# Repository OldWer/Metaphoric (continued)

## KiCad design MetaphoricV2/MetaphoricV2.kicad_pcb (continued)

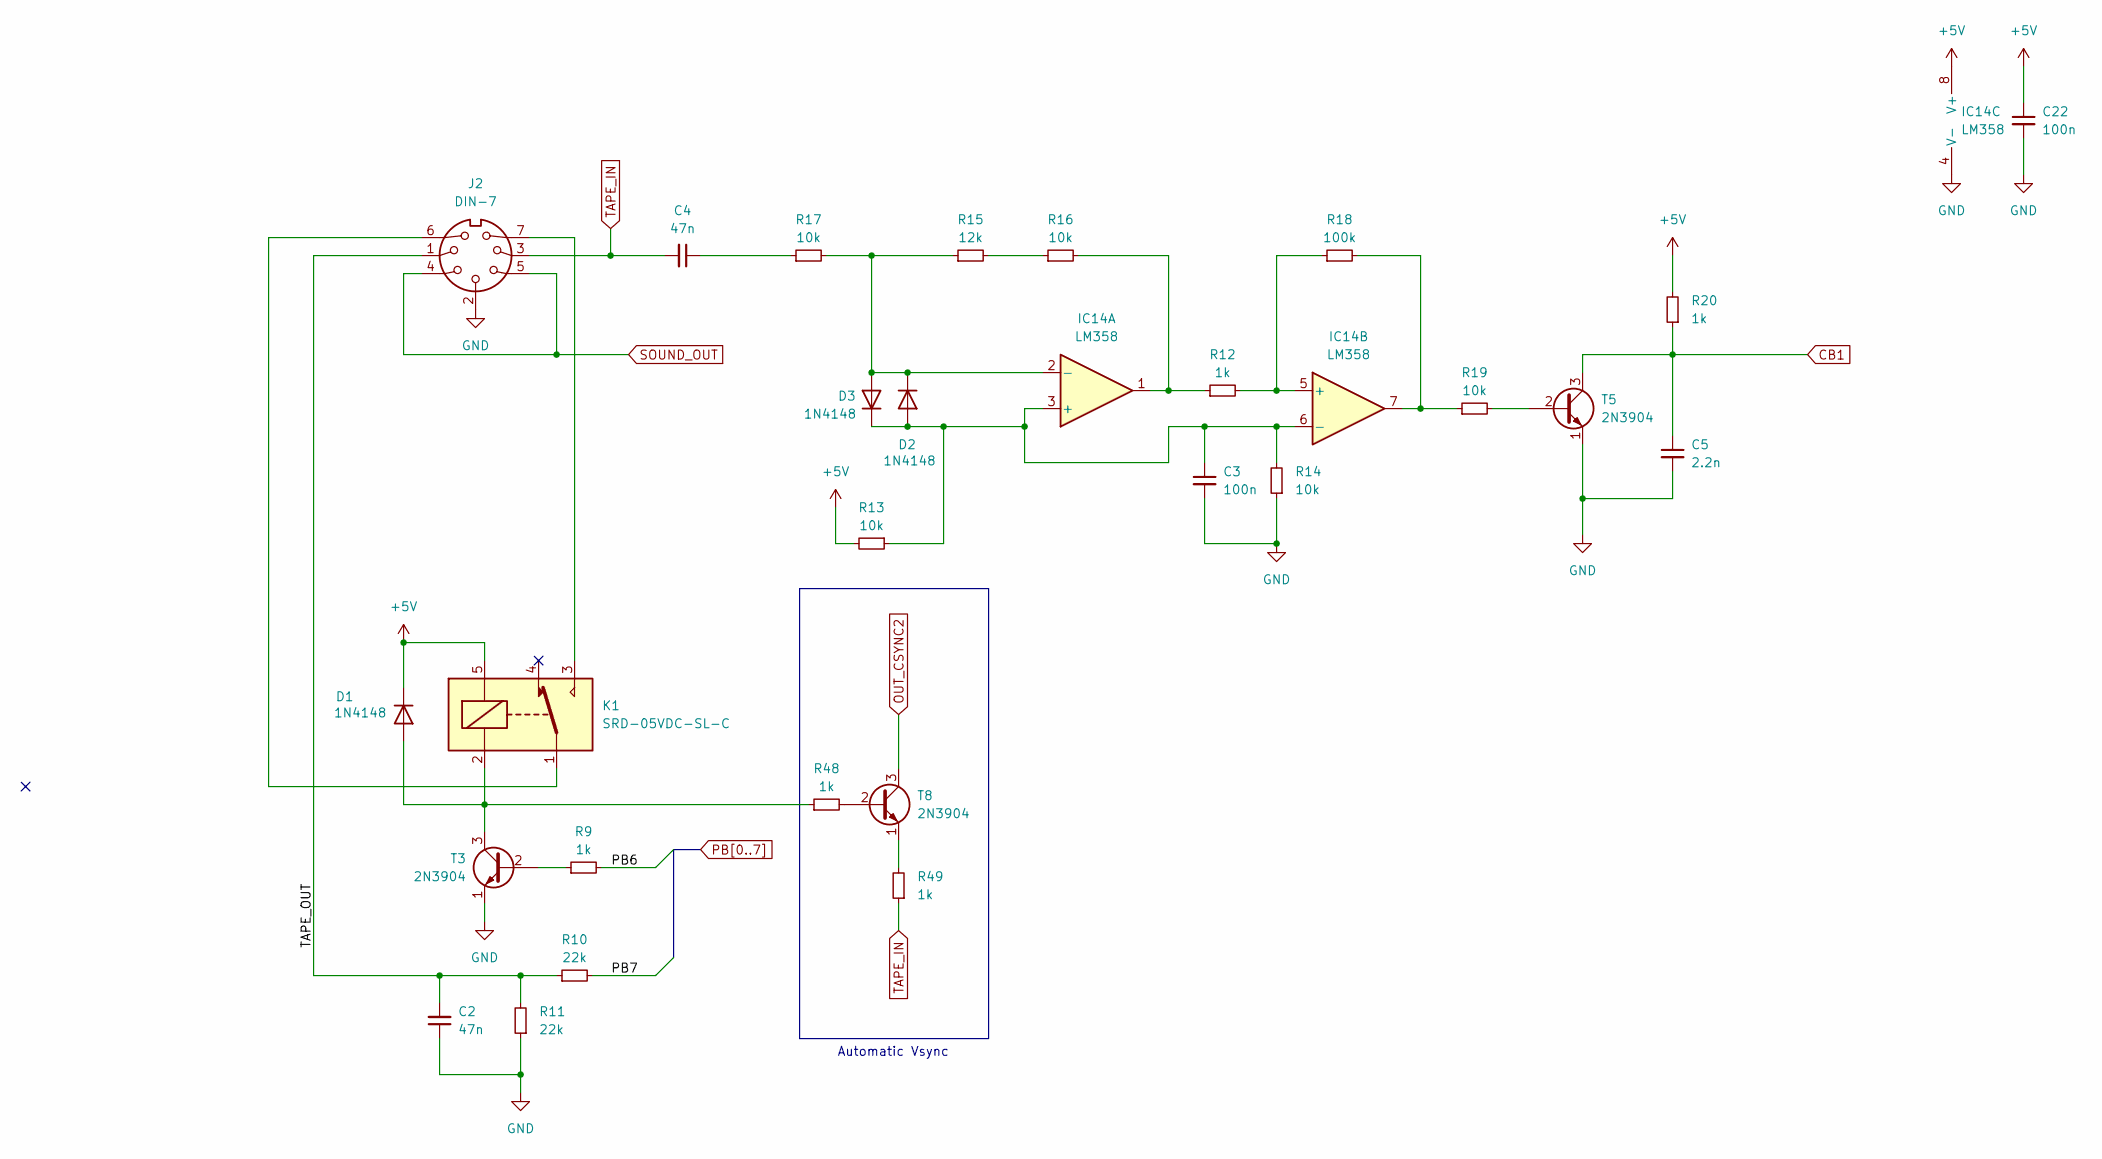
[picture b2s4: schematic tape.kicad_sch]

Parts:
C2, C4: 47n; C_Disc_D5.0mm_W2.5mm_P5.00mm
C3, C22: 100n; C_Disc_D5.0mm_W2.5mm_P5.00mm
C5: 2.2n; C_Disc_D5.0mm_W2.5mm_P5.00mm
D1, D2, D3: 1N4148; D_DO-35_SOD27_P7.62mm_Horizontal
IC14: LM358; DIP-8_W7.62mm_LongPads
J2: DIN-7; AV_CON_DIN7
K1: SRD-05VDC-SL-C; Relay_SPDT_SANYOU_SRD_Series_Form_C
R9, R12, R20, R48, R49: 1k; R_Axial_DIN0207_L6.3mm_D2.5mm_P7.62mm_Horizontal
R10, R11: 22k; R_Axial_DIN0207_L6.3mm_D2.5mm_P7.62mm_Horizontal
R13, R14, R16, R17, R19: 10k; R_Axial_DIN0207_L6.3mm_D2.5mm_P7.62mm_Horizontal
R15: 12k; R_Axial_DIN0207_L6.3mm_D2.5mm_P7.62mm_Horizontal
R18: 100k; R_Axial_DIN0207_L6.3mm_D2.5mm_P7.62mm_Horizontal
T3, T5, T8: 2N3904; TO-92_Inline

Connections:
+5V: C22.1, D1.1 (K), IC14.8 (V+), K1.5, R13.2, R20.2; also elsewhere on the board
/Tape/TAPE_OUT: C2.2, J2.1, R10.1, R11.2
CB1: C5.1, R20.1, T5.3 (C); also elsewhere on the board
GND: C2.1, C3.2, C5.2, C22.2, IC14.4 (V-), J2.2, R11.1, R14.1, T3.1 (E), T5.1 (E); also elsewhere on the board
unnamed: C4.1, R17.1
unnamed: D1.2 (A), K1.2, R48.1, T3.3 (C)
unnamed: C3.1, D2.2 (A), D3.1 (K), IC14.3 (+), IC14.6 (-), R13.1, R14.2
unnamed: D2.1 (K), D3.2 (A), IC14.2 (-), R15.1, R17.2
unnamed: IC14.1, R12.1, R16.2
unnamed: IC14.7, R18.2, R19.1
unnamed: IC14.5 (+), R12.2, R18.1
unnamed: J2.6, K1.1
unnamed: J2.7, K1.3
unnamed: R15.2, R16.1
unnamed: R9.1, T3.2 (B)
unnamed: R19.2, T5.2 (B)
unnamed: R48.2, T8.2 (B)
unnamed: R49.2, T8.1 (E)
OUT_CSYNC2: T8.3 (C); also elsewhere on the board
PB6: R9.2; also elsewhere on the board
PB7: R10.2; also elsewhere on the board
SOUND_OUT: J2.4, J2.5; also elsewhere on the board
TAPE_IN: C4.2, J2.3, R49.1

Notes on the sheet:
Automatic Vsync

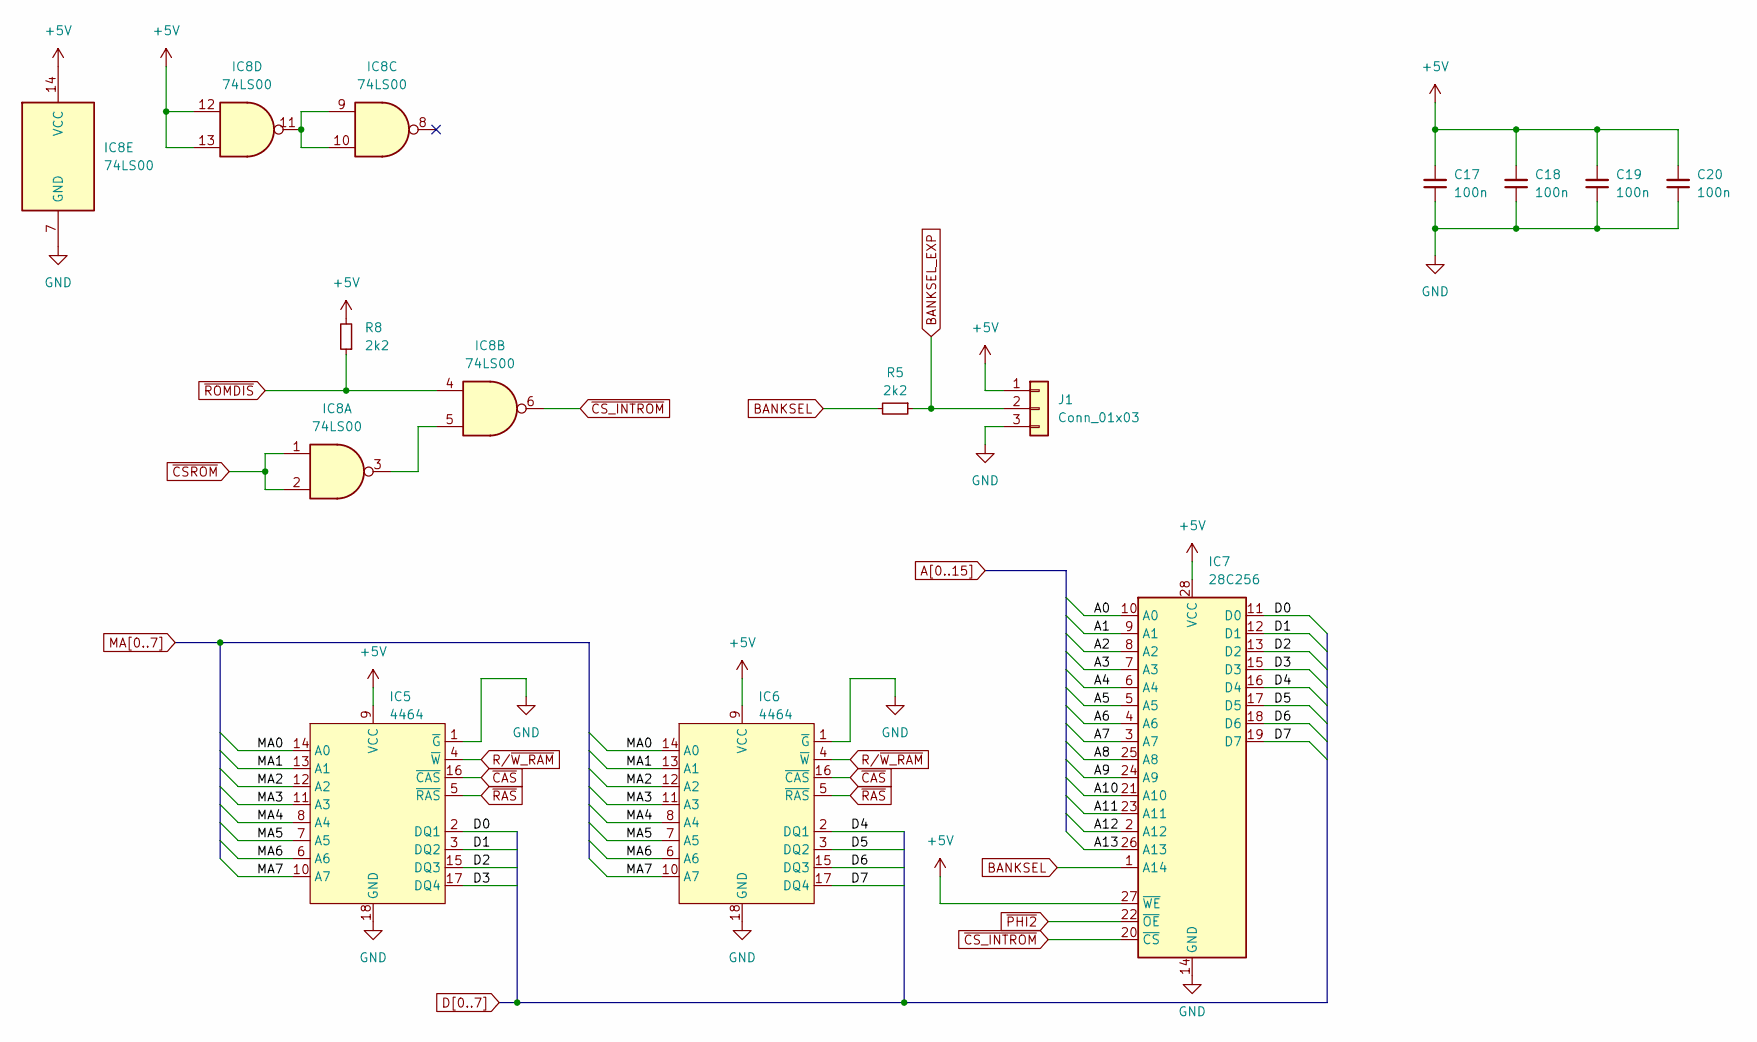
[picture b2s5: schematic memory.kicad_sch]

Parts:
C17, C18, C19, C20: 100n; C_Disc_D5.0mm_W2.5mm_P5.00mm
IC5, IC6: 4464; DIP-18_W7.62mm_LongPads
IC7: 28C256; DIP-28_W15.24mm_LongPads
IC8: 74LS00; DIP-14_W7.62mm_LongPads
J1: Conn_01x03; PinHeader_1x03_P2.54mm_Vertical
R5, R8: 2k2; R_Axial_DIN0207_L6.3mm_D2.5mm_P7.62mm_Horizontal

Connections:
+5V: C17.2, C18.2, C19.2, C20.2, IC5.9 (VCC), IC6.9 (VCC), IC7.27 (~WE), IC7.28 (VCC), IC8.12, IC8.13, IC8.14 (VCC), J1.1, R8.2; also elsewhere on the board
A0: IC7.10 (A0); also elsewhere on the board
A1: IC7.9 (A1); also elsewhere on the board
A2: IC7.8 (A2); also elsewhere on the board
A3: IC7.7 (A3); also elsewhere on the board
A4: IC7.6 (A4); also elsewhere on the board
A5: IC7.5 (A5); also elsewhere on the board
A6: IC7.4 (A6); also elsewhere on the board
A7: IC7.3 (A7); also elsewhere on the board
A8: IC7.25 (A8); also elsewhere on the board
A9: IC7.24 (A9); also elsewhere on the board
A10: IC7.21 (A10); also elsewhere on the board
A11: IC7.23 (A11); also elsewhere on the board
A12: IC7.2 (A12); also elsewhere on the board
A13: IC7.26 (A13); also elsewhere on the board
BANKSEL: IC7.1 (A14), R5.2
BANKSEL_EXP: J1.2, R5.1; also elsewhere on the board
D0: IC5.2 (DQ1), IC7.11 (D0); also elsewhere on the board
D1: IC5.3 (DQ2), IC7.12 (D1); also elsewhere on the board
D2: IC5.15 (DQ3), IC7.13 (D2); also elsewhere on the board
D3: IC5.17 (DQ4), IC7.15 (D3); also elsewhere on the board
D4: IC6.2 (DQ1), IC7.16 (D4); also elsewhere on the board
D5: IC6.3 (DQ2), IC7.17 (D5); also elsewhere on the board
D6: IC6.15 (DQ3), IC7.18 (D6); also elsewhere on the board
D7: IC6.17 (DQ4), IC7.19 (D7); also elsewhere on the board
GND: C17.1, C18.1, C19.1, C20.1, IC5.1 (~G), IC5.18 (GND), IC6.1 (~G), IC6.18 (GND), IC7.14 (GND), IC8.7 (GND), J1.3; also elsewhere on the board
MA0: IC5.14 (A0), IC6.14 (A0); also elsewhere on the board
MA1: IC5.13 (A1), IC6.13 (A1); also elsewhere on the board
MA2: IC5.12 (A2), IC6.12 (A2); also elsewhere on the board
MA3: IC5.11 (A3), IC6.11 (A3); also elsewhere on the board
MA4: IC5.8 (A4), IC6.8 (A4); also elsewhere on the board
MA5: IC5.7 (A5), IC6.7 (A5); also elsewhere on the board
MA6: IC5.6 (A6), IC6.6 (A6); also elsewhere on the board
MA7: IC5.10 (A7), IC6.10 (A7); also elsewhere on the board
unnamed: IC8.3, IC8.5
unnamed: IC8.9, IC8.10, IC8.11
R/~W_RAM: IC5.4 (~W), IC6.4 (~W); also elsewhere on the board
~CAS: IC5.16 (~CAS), IC6.16 (~CAS); also elsewhere on the board
~CSROM: IC8.1, IC8.2; also elsewhere on the board
~CS_INTROM: IC7.20 (~CS), IC8.6
~PHI2: IC7.22 (~OE); also elsewhere on the board
~RAS: IC5.5 (~RAS), IC6.5 (~RAS); also elsewhere on the board
~ROMDIS: IC8.4, R8.1; also elsewhere on the board

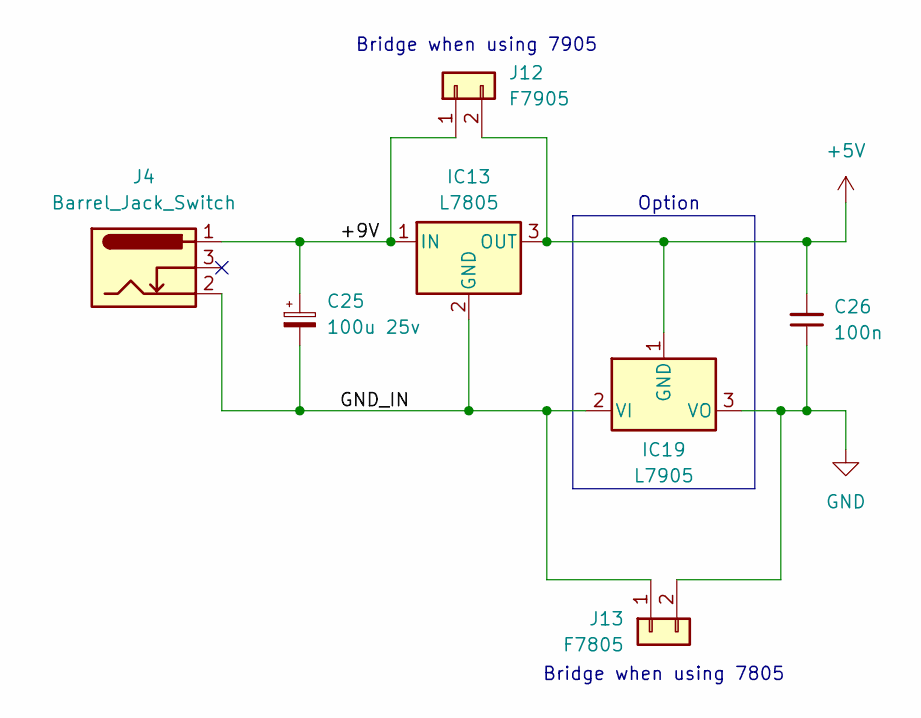
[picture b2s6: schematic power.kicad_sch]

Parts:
C25: 100u 25v; CP_Radial_D8.0mm_P3.50mm
C26: 100n; C_Disc_D5.0mm_W2.5mm_P5.00mm
IC13: L7805; TO-220-3_Vertical
IC19: L7905; TO-220-3_Vertical
J4: Barrel_Jack_Switch; BarrelJack_Horizontal
J12: F7905; PinHeader_1x02_P2.54mm_Vertical
J13: F7805; PinHeader_1x02_P2.54mm_Vertical

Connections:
+5V: C26.2, IC13.3 (OUT), IC19.1 (GND), J12.2; also elsewhere on the board
/Power/+9V: C25.1, IC13.1 (IN), J4.1, J12.1
/Power/GND_IN: C25.2, IC13.2 (GND), IC19.2 (VI), J4.2, J13.1
GND: C26.1, IC19.3 (VO), J13.2; also elsewhere on the board

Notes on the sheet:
Bridge when using 7805
Option
Bridge when using 7905

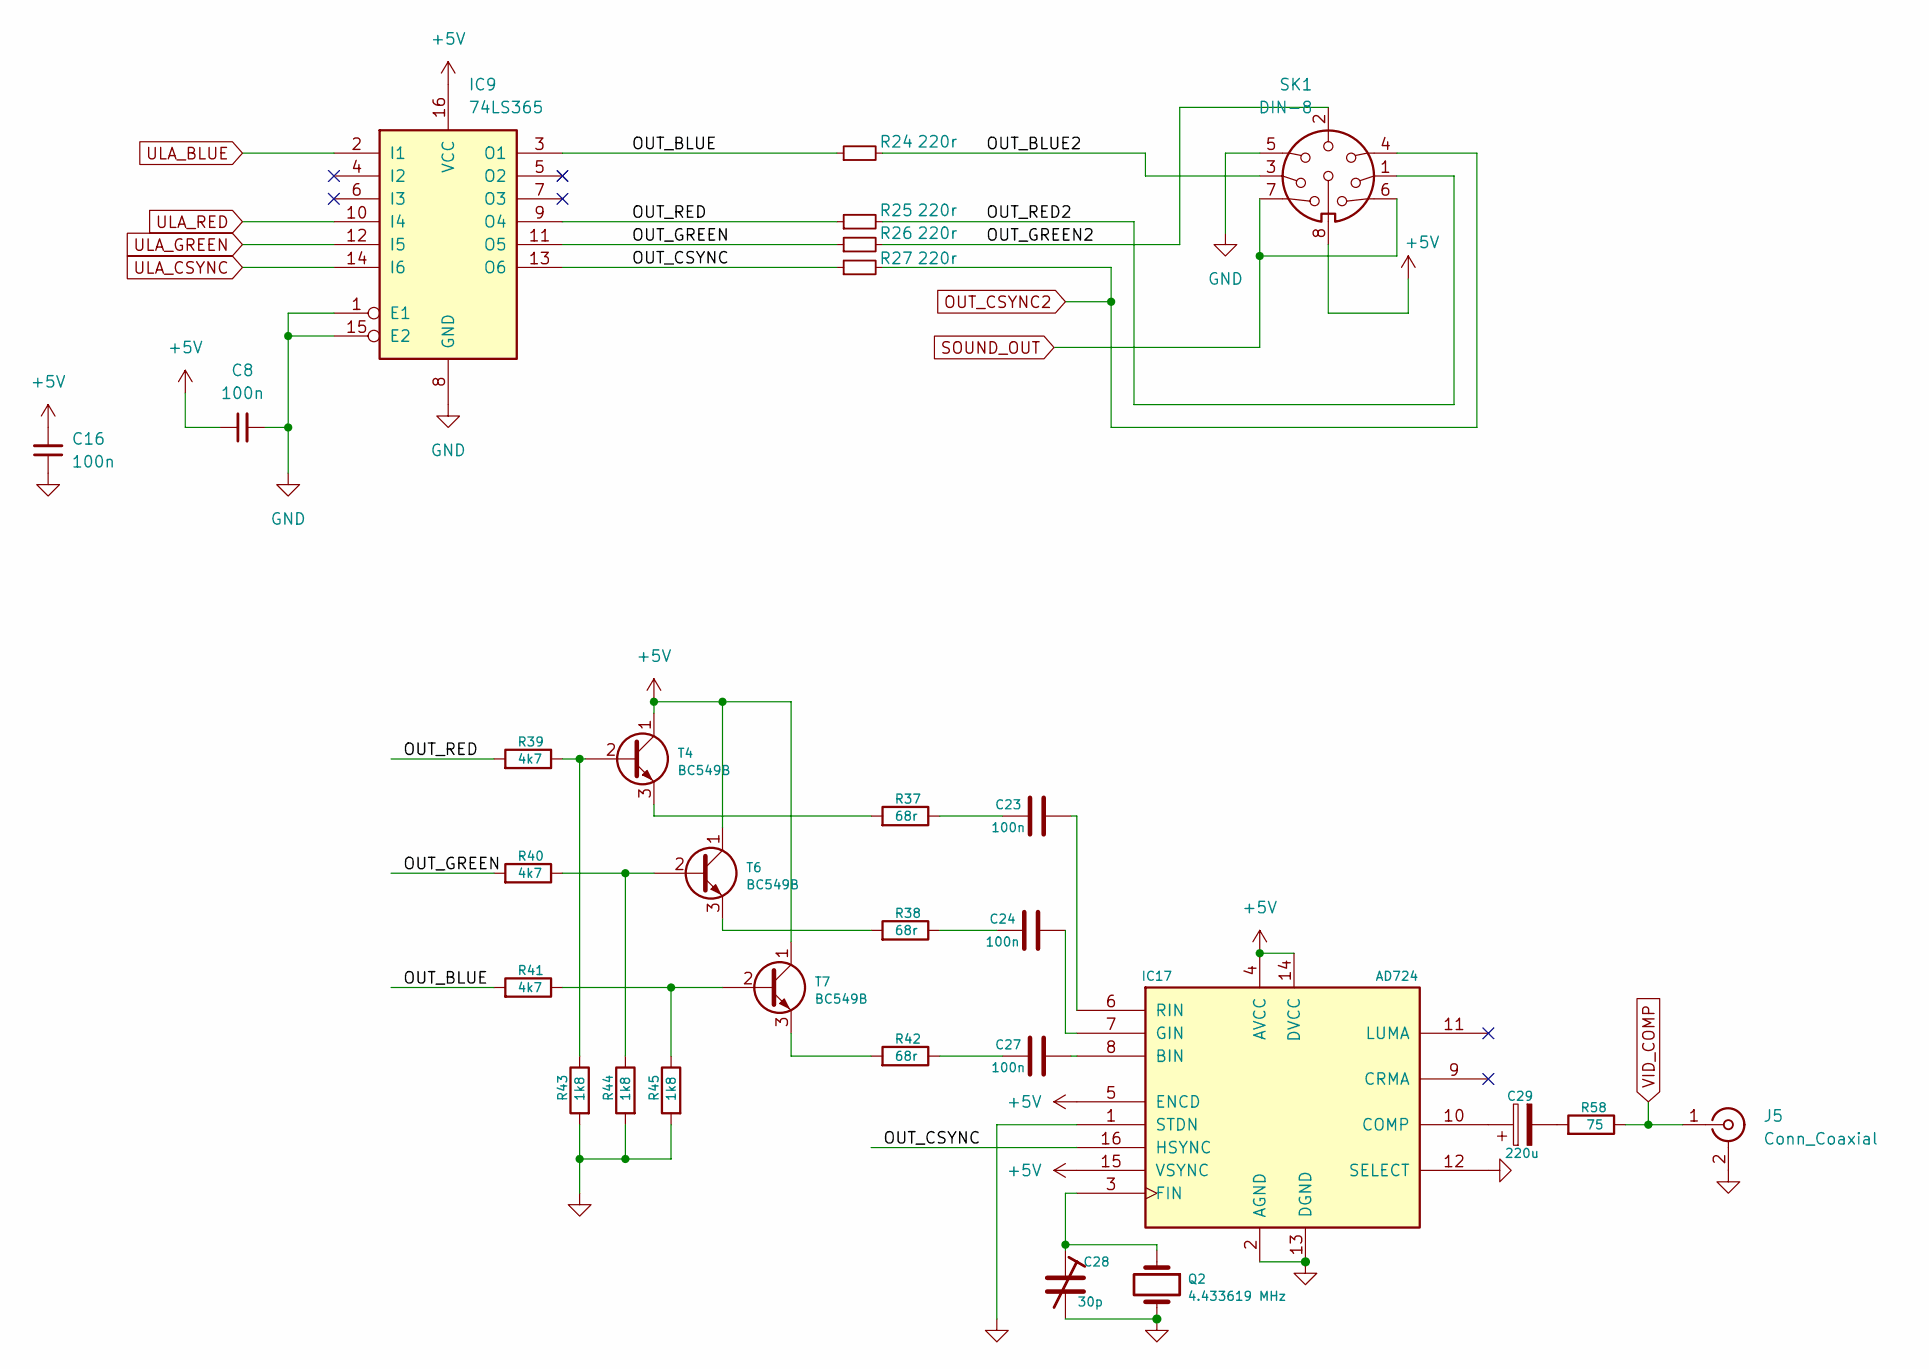
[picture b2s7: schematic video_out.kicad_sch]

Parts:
C8, C16, C23, C24, C27: 100n; C_Disc_D5.0mm_W2.5mm_P5.00mm
C28: 30p; C_Trim_D6.3mm_P5.50mm
C29: 220u; CP_Radial_D5.0mm_P2.50mm
IC9: 74LS365; DIP-16_W7.62mm_LongPads
IC17: AD724; SOIC-16W_7.5x10.3mm_P1.27mm
J5: Conn_Coaxial; Composite_RCA
Q2: 4.433619 MHz; Crystal_HC49-U_Vertical
R24, R25, R26, R27: 220r; R_Axial_DIN0207_L6.3mm_D2.5mm_P7.62mm_Horizontal
R37, R38, R42: 68r; R_Axial_DIN0207_L6.3mm_D2.5mm_P7.62mm_Horizontal
R39, R40, R41: 4k7; R_Axial_DIN0207_L6.3mm_D2.5mm_P7.62mm_Horizontal
R43, R44, R45: 1k8; R_Axial_DIN0207_L6.3mm_D2.5mm_P7.62mm_Horizontal
R58: 75; R_Axial_DIN0207_L6.3mm_D2.5mm_P7.62mm_Horizontal
SK1: DIN-8; AV_CON_DIN8
T4, T6, T7: BC549B; TO-92

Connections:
+5V: C8.1, C16.2, IC9.16 (VCC), IC17.4 (AVCC), IC17.5 (ENCD), IC17.14 (DVCC), IC17.15 (VSYNC), SK1.8, T4.1 (C), T6.1 (C), T7.1 (C); also elsewhere on the board
/Video Out/OUT_BLUE: IC9.3 (O1), R24.1, R41.2
/Video Out/OUT_BLUE2: R24.2, SK1.3
/Video Out/OUT_CSYNC: IC9.13 (O6), IC17.16 (HSYNC), R27.1
/Video Out/OUT_GREEN: IC9.11 (O5), R26.1, R40.2
/Video Out/OUT_GREEN2: R26.2, SK1.2
/Video Out/OUT_RED: IC9.9 (O4), R25.1, R39.2
/Video Out/OUT_RED2: R25.2, SK1.1
GND: C8.2, C16.1, C28.2, IC9.1 (E1), IC9.8 (GND), IC9.15 (E2), IC17.1 (STDN), IC17.2 (AGND), IC17.12 (SELECT), IC17.13 (DGND), J5.2 (Ext), Q2.2, R43.2, R44.2, R45.2, SK1.5; also elsewhere on the board
unnamed: C23.1, R37.1
unnamed: C24.1, R38.1
unnamed: C27.1, R42.1
unnamed: C29.2, R58.2
unnamed: C27.2, IC17.8 (BIN)
unnamed: C29.1, IC17.10 (COMP)
unnamed: C28.1, IC17.3 (FIN), Q2.1
unnamed: C24.2, IC17.7 (GIN)
unnamed: C23.2, IC17.6 (RIN)
unnamed: R39.1, R43.1, T4.2 (B)
unnamed: R37.2, T4.3 (E)
unnamed: R40.1, R44.1, T6.2 (B)
unnamed: R38.2, T6.3 (E)
unnamed: R41.1, R45.1, T7.2 (B)
unnamed: R42.2, T7.3 (E)
OUT_CSYNC2: R27.2, SK1.4; also elsewhere on the board
SOUND_OUT: SK1.6, SK1.7; also elsewhere on the board
ULA_BLUE: IC9.2 (I1); also elsewhere on the board
ULA_CSYNC: IC9.14 (I6); also elsewhere on the board
ULA_GREEN: IC9.12 (I5); also elsewhere on the board
ULA_RED: IC9.10 (I4); also elsewhere on the board
VID_COMP: J5.1 (In), R58.1; also elsewhere on the board

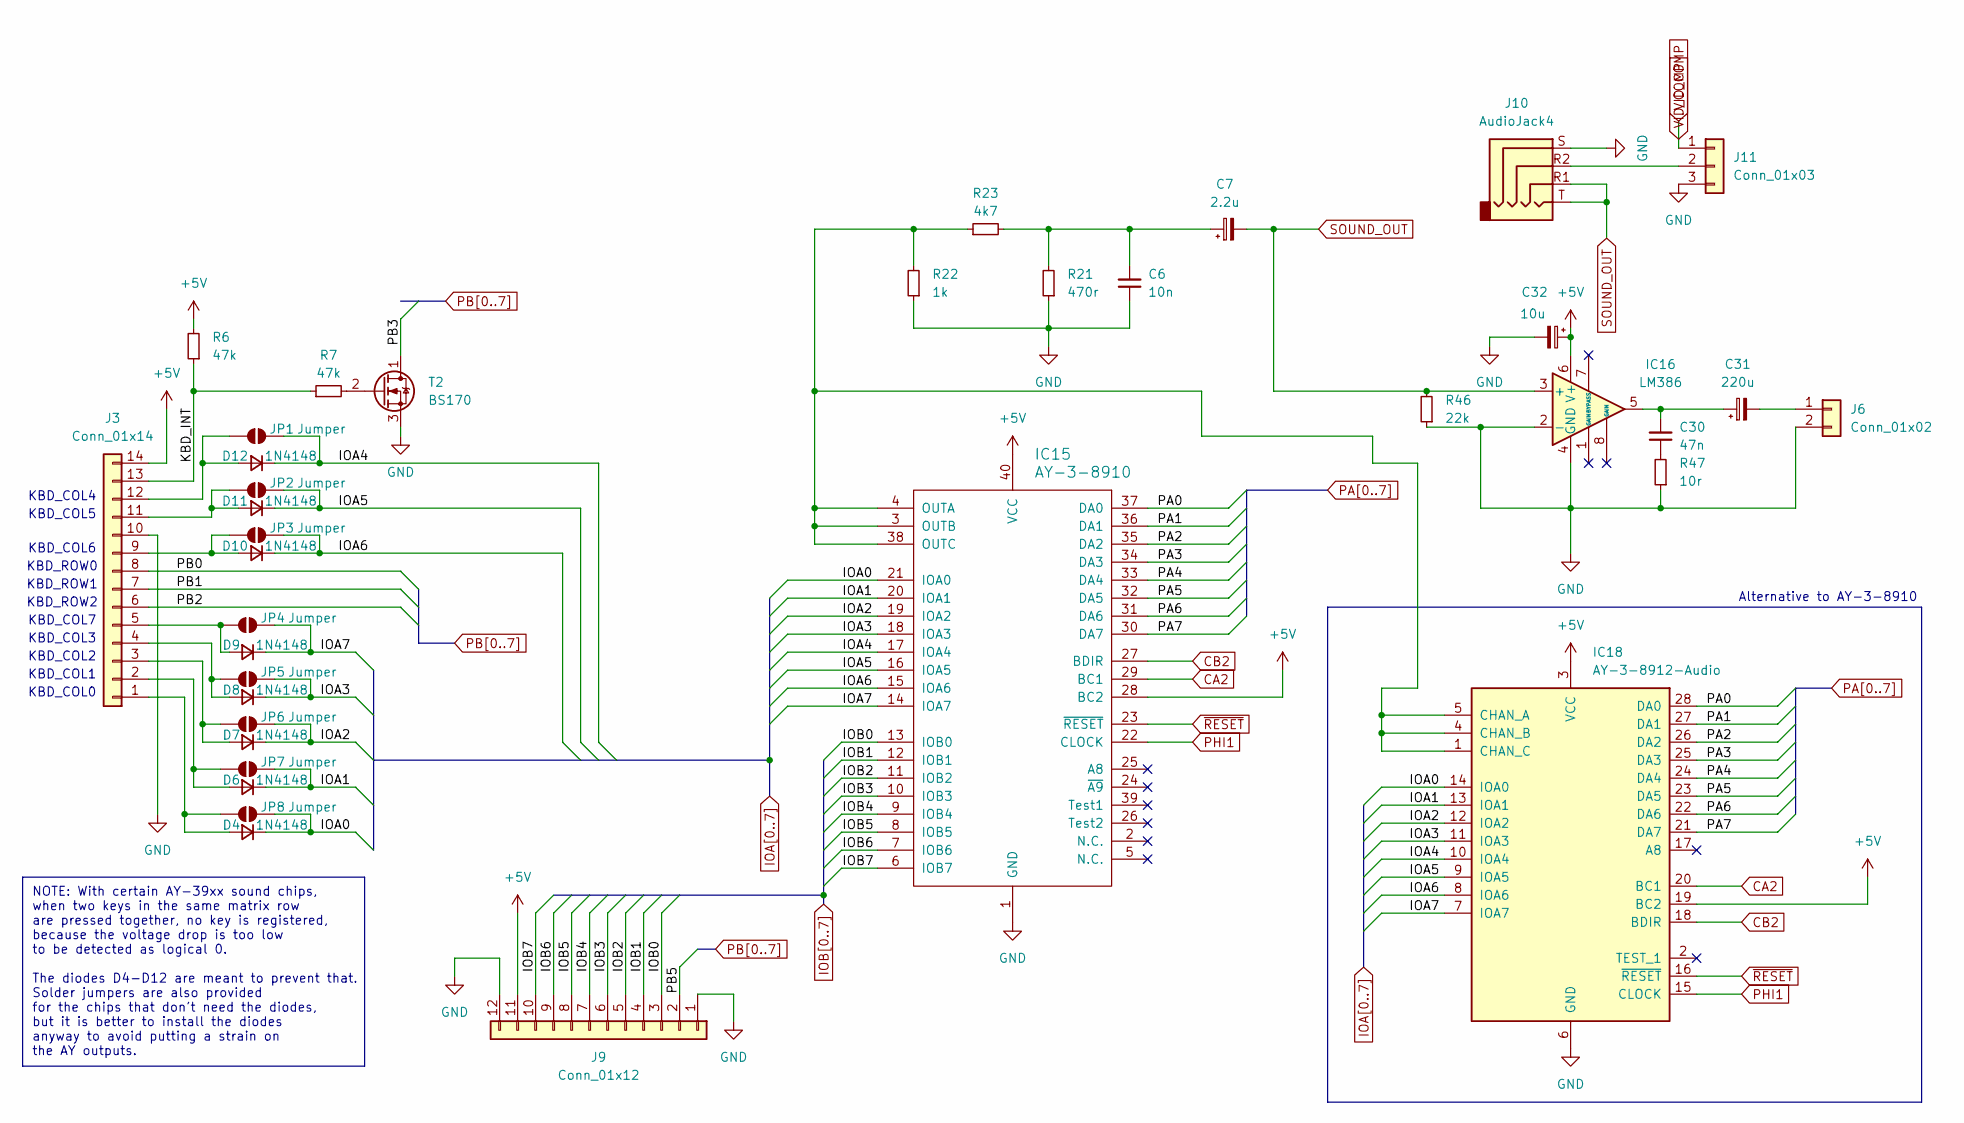
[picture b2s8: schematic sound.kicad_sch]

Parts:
C6: 10n; C_Disc_D5.0mm_W2.5mm_P5.00mm
C7: 2.2u; CP_Radial_D5.0mm_P2.50mm
C30: 47n; C_Disc_D5.0mm_W2.5mm_P5.00mm
C31: 220u; CP_Radial_D5.0mm_P2.50mm
C32: 10u; CP_Radial_D5.0mm_P2.50mm
D4, D6, D7, D8, D9, D10, D11, D12: 1N4148; D_DO-35_SOD27_P7.62mm_Horizontal
IC15: AY-3-8910; DIP-40_W15.24mm_LongPads
IC16: LM386; DIP-8_W7.62mm
IC18: AY-3-8912-Audio; DIP-28_W15.24mm_LongPads
J3: Conn_01x14; PinHeader_1x14_P2.54mm_Vertical
J6: Conn_01x02; PinHeader_1x02_P2.54mm_Vertical
J9: Conn_01x12; PinHeader_1x12_P2.54mm_Vertical
J10: AudioJack4; PJ-322
J11: Conn_01x03; PinHeader_1x03_P2.54mm_Vertical
JP1, JP2, JP3, JP4, JP5, JP6, JP7, JP8: Jumper; SolderJumper-2_P1.3mm_Open_RoundedPad1.0x1.5mm
R6, R7: 47k; R_Axial_DIN0207_L6.3mm_D2.5mm_P7.62mm_Horizontal
R21: 470r; R_Axial_DIN0207_L6.3mm_D2.5mm_P7.62mm_Horizontal
R22: 1k; R_Axial_DIN0207_L6.3mm_D2.5mm_P7.62mm_Horizontal
R23: 4k7; R_Axial_DIN0207_L6.3mm_D2.5mm_P7.62mm_Horizontal
R46: 22k; R_Axial_DIN0207_L6.3mm_D2.5mm_P7.62mm_Horizontal
R47: 10r; R_Axial_DIN0207_L6.3mm_D2.5mm_P7.62mm_Horizontal
T2: BS170; TO-92_Inline

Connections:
+5V: C32.1, IC15.28 (BC2), IC15.40 (VCC), IC16.6 (V+), IC18.3 (VCC), IC18.19 (BC2), J3.14, J9.11, R6.2; also elsewhere on the board
/Sound/KBD_INT: J3.13, R6.1, R7.1
CA2: IC15.29 (BC1), IC18.20 (BC1); also elsewhere on the board
CB2: IC15.27 (BDIR), IC18.18 (BDIR); also elsewhere on the board
GND: C6.1, C32.2, IC15.1 (GND), IC16.2 (-), IC16.4 (GND), IC18.6 (GND), J3.10, J6.2, J9.1, J9.12, J10.S, J11.3, R21.1, R22.1, R46.1, R47.1, T2.3 (S); also elsewhere on the board
IOA0: D4.1 (K), IC15.21 (IOA0), IC18.14 (IOA0), JP8.2 (B)
IOA1: D6.1 (K), IC15.20 (IOA1), IC18.13 (IOA1), JP7.2 (B)
IOA2: D7.1 (K), IC15.19 (IOA2), IC18.12 (IOA2), JP6.2 (B)
IOA3: D8.1 (K), IC15.18 (IOA3), IC18.11 (IOA3), JP5.2 (B)
IOA4: D12.1 (K), IC15.17 (IOA4), IC18.10 (IOA4), JP1.2 (B)
IOA5: D11.1 (K), IC15.16 (IOA5), IC18.9 (IOA5), JP2.2 (B)
IOA6: D10.1 (K), IC15.15 (IOA6), IC18.8 (IOA6), JP3.2 (B)
IOA7: D9.1 (K), IC15.14 (IOA7), IC18.7 (IOA7), JP4.2 (B)
IOB0: IC15.13 (IOB0), J9.3
IOB1: IC15.12 (IOB1), J9.4
IOB2: IC15.11 (IOB2), J9.5
IOB3: IC15.10 (IOB3), J9.6
IOB4: IC15.9 (IOB4), J9.7
IOB5: IC15.8 (IOB5), J9.8
IOB6: IC15.7 (IOB6), J9.9
IOB7: IC15.6 (IOB7), J9.10
unnamed: C6.2, C7.1, R21.2, R23.2
unnamed: C30.1, R47.2
unnamed: C30.2, C31.1, IC16.5
unnamed: D4.2 (A), J3.1, JP8.1 (A)
unnamed: D6.2 (A), J3.2, JP7.1 (A)
unnamed: D7.2 (A), J3.3, JP6.1 (A)
unnamed: D8.2 (A), J3.4, JP5.1 (A)
unnamed: D9.2 (A), J3.5, JP4.1 (A)
unnamed: D10.2 (A), J3.9, JP3.1 (A)
unnamed: D11.2 (A), J3.11, JP2.1 (A)
unnamed: D12.2 (A), J3.12, JP1.1 (A)
unnamed: IC15.3 (OUTB), IC15.4 (OUTA), IC15.38 (OUTC), IC18.1 (CHAN_C), IC18.4 (CHAN_B), IC18.5 (CHAN_A), R22.2, R23.1
unnamed: C31.2, J6.1
unnamed: J10.R2, J11.2
unnamed: R7.2, T2.2 (G)
PA0: IC15.37 (DA0), IC18.28 (DA0); also elsewhere on the board
PA1: IC15.36 (DA1), IC18.27 (DA1); also elsewhere on the board
PA2: IC15.35 (DA2), IC18.26 (DA2); also elsewhere on the board
PA3: IC15.34 (DA3), IC18.25 (DA3); also elsewhere on the board
PA4: IC15.33 (DA4), IC18.24 (DA4); also elsewhere on the board
PA5: IC15.32 (DA5), IC18.23 (DA5); also elsewhere on the board
PA6: IC15.31 (DA6), IC18.22 (DA6); also elsewhere on the board
PA7: IC15.30 (DA7), IC18.21 (DA7); also elsewhere on the board
PB0: J3.8; also elsewhere on the board
PB1: J3.7; also elsewhere on the board
PB2: J3.6; also elsewhere on the board
PB3: T2.1 (D); also elsewhere on the board
PB5: J9.2; also elsewhere on the board
PHI1: IC15.22 (CLOCK), IC18.15 (CLOCK); also elsewhere on the board
SOUND_OUT: C7.2, IC16.3 (+), J10.R1, J10.T, R46.2; also elsewhere on the board
VID_COMP: J11.1; also elsewhere on the board
~RESET: IC15.23 (~RESET), IC18.16 (~RESET); also elsewhere on the board

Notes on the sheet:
NOTE: With certain AY-39xx sound chips, when two keys in the same matrix row are pressed together, no key is registered, because the voltage drop is too low to be detected as logical 0. The diodes D4-D12 are meant to prevent that. Solder jumpers are also provided for the chips that don't need the d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
KBD_COL6
KBD_COL4
KBD_ROW0
KBD_ROW2
KBD_COL0
Alternative to AY-3-8910
KBD_COL3
KBD_ROW1
KBD_COL7
KBD_COL1
KBD_COL5
KBD_COL2

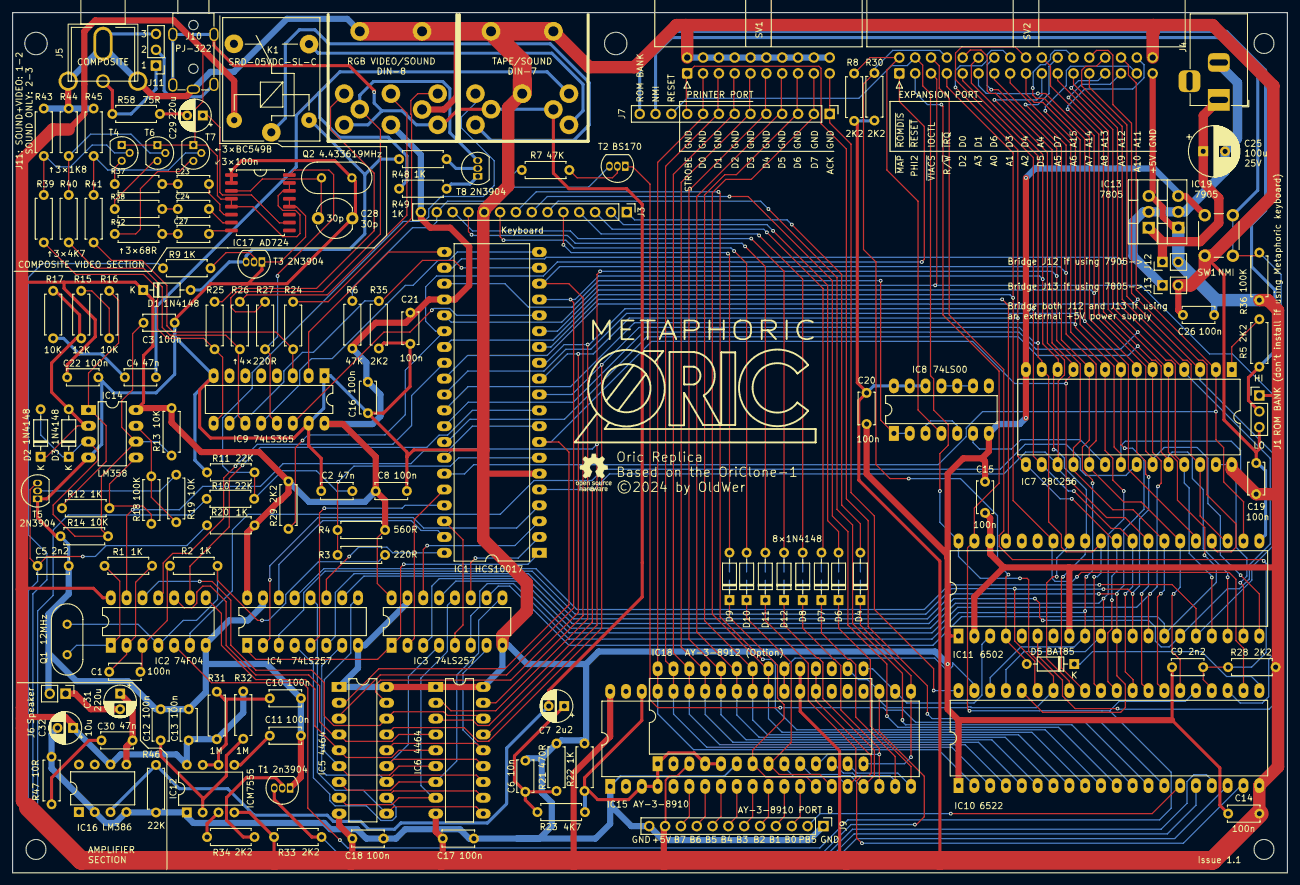
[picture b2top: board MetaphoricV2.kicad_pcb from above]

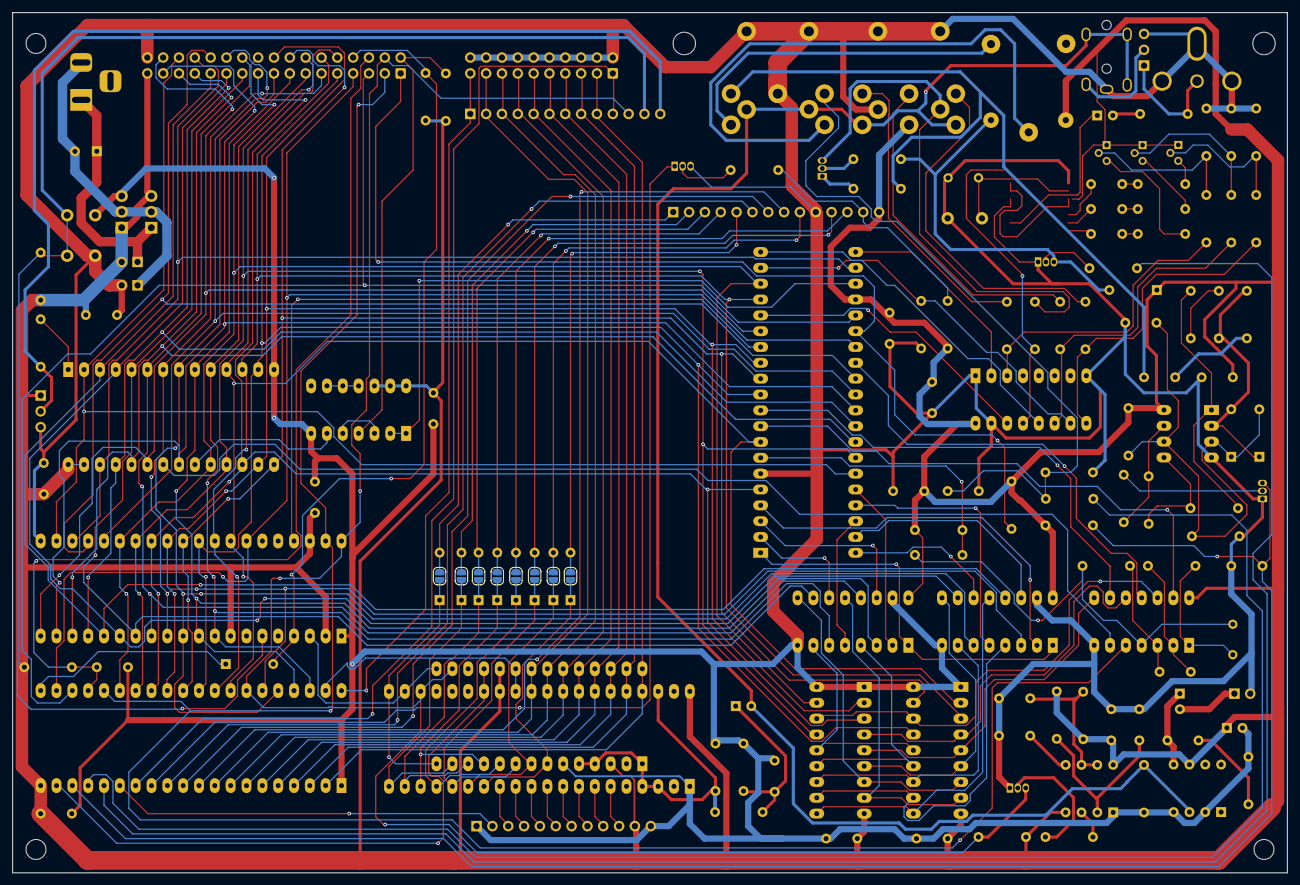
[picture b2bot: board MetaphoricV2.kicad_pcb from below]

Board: 2 copper layers, 204.5 x 138.0 mm, 148 parts (8 on the bottom side), 177 nets.

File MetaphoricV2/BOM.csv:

Reference;Value;Footprint;Qty;Notes;;;;;;;
CAPACITORS;;;;;DIP SOCKETS;;;;;;
"C1;C3;C8;C10;C11;C12;C13;C14;C15;C16;
C17;C18;C19;C20;C21;C22;C23;C24;C26;C27";100n;Ceramic capacitor ;20;;DIP14;2;;;;;
"C2;C4;C30";47n;Ceramic capacitor ;3;;DIP16;3;;;;;
"C5;C9";2.2n;Ceramic capacitor ;2;;DIP18;2;;;;;
C6;10n;Ceramic capacitor ;1;;DIP28;1;;;;;
C7;2.2u;Electrolytic capacitor;1;;DIP40;4;;;;;
C25;100u 25v;Electrolytic capacitor;1;;DIP8;3;;;;;
C28;30p;Trimmer;1;;;;;;;;
"C29;C31";220u;Electrolytic capacitor;2;;;;;;;;
C32;10u;Electrolytic capacitor;1;;;;;;;;
DIODES;;;;;;;;;;;
"D1;D2;D3;D4;D6;D7;D8;D9;D10;D11;D12";1N4148;DO-35;11;;;;;;;;
D5;BAT85;DO-35;1;;;;;;;;
INTEGRATED CIRCUITS;;;;;;;;;;;
IC2;74F04;DIP14;1;;;;;;;;
IC8;74LS00;DIP14;1;;;;;;;;
"IC3;IC4";74LS257;DIP16;2;;;;;;;;
IC9;74LS365;DIP16;1;;;;;;;;
"IC5;IC6";MEMORY 4464;DIP18;2;;;;;;;;
IC7;28C256;DIP28;1;;;;;;;;
IC1;HCS10017;DIP40;1;;;;;;;;
IC10;CPU 6522;DIP40;1;;;;;;;;
IC11;VIA 6502;DIP40;1;;;;;;;;
IC15;AY-3-8910;DIP40;1;;;;;;;;
IC12;ICM7555xP;DIP8;1;;;;;;;;
IC14;LM358;DIP8;1;;;;;;;;
IC16;LM386;DIP8;1;;;;;;;;
IC17;AD724;SOIC-16W;1;;;;;;;;
VOLTAGE REGULATOR;;;;;;;;;;;
IC13/IC19;L7805/L7905;TO-220-3;1;;;;;;;;
CONNECTORS;;;;;;;;;;;
"J1;J11";Conn_01x03;PinHeader_1x03;2;(35 pins total);;;;;;;
J2;DIN-7;DIN7 Socket;1;Tape;;;;;;;
SK1;DIN-8;DIN8 Socket;1;Video;;;;;;;
J3;Conn_01x14;PinHeader_1x14;1;Keyboard;;;;;;;
J4;Barrel_Jack;Barrel Jack;1;Power;;;;;;;
J5;Conn_Coaxial;RCA Socket;1;Composite;;;;;;;
J6;Conn_01x02;PinHeader_1x02;1;Speaker;;;;;;;
J7;Joystick;PinHeader_1x13;1;Keyboard 2;;;;;;;
J9;Conn_01x12;PinHeader_1x12;1;Unpopulated;;;;;;;
J10;AudioJack4;TRRS Socket PJ-322;1;Audio/Video;;;;;;;
SV1;Printer;IDC-Header_2x10;1;;;;;;;;
SV2;Expansion;IDC-Header_2x17;1;;;;;;;;
RELAY;;;;;;;;;;;
K1;SRD-05VDC-SL-C;Relay;1;;;;;;;;
CRYSTALS;;;;;;;;;;;
Q1;12MHz;Crystal_HC49-U;1;;;;;;;;
Q2;4.433619 MHz;Crystal_HC49-U;1;;;;;;;;
RESISTORS;;;;;;;;;;;
"R1;R2;R9;R12;R20;R22;R48;R49";1k;Resistor;8;;;;;;;;
R3;220r;Resistor;1;;;;;;;;
R4;560r;Resistor;1;;;;;;;;
"R5;R8;R28;R29;R30;R33;R34;R35";2k2;Resistor;8;;;;;;;;
"R6;R7";47k;Resistor;2;;;;;;;;
"R10;R11;R46";22k;Resistor;3;;;;;;;;
"R13;R14;R16;R17;R19";10k;Resistor;5;;;;;;;;
R15;12k;Resistor;1;;;;;;;;
"R18;R36";100k;Resistor;2;;;;;;;;
R21;470r;Resistor;1;;;;;;;;
"R23;R39;R40;R41";4k7;Resistor;4;;;;;;;;
"R24;R25;R26;R27";220r;Resistor;4;;;;;;;;
"R31;R32";1M;Resistor;2;;;;;;;;
"R37;R38;R42";68r;Resistor;3;;;;;;;;
"R43;R44;R45";1k8;Resistor;3;;;;;;;;
R47;10r;Resistor;1;;;;;;;;
R58;75r;Resistor;1;;;;;;;;
BUTTON;;;;;;;;;;;
SW1;SW_Push;Tact Switch;1;;;;;;;;
TRANSISTORS;;;;;;;;;;;
"T1;T3;T5;T8";2N3904;Transistor;4;;;;;;;;
T2;BS170;Transistor;1;;;;;;;;
"T4;T6;T7";BC549B;Transistor;3;;;;;;;;
;;;;;;;;;;;
;;;;;;;;;;;
;;;;;;;;;;;28
